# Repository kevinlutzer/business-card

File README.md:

# Electronic Business Card 

The purpose of this project was to demonstrate some of my skills as an Electrical Engineer to potential employers. This project required me to build and prototype a tri-state circuit, add controls with a STM32G ARM microcontroller and design/manufacture a custom printed circuit board. When you plug the device into a standard USB2A port it scrolls my portfolio website's URL across the matrix display. I designed this device to cost about $2.50 CAD per populated board. 

This idea was inspired by a piece of advice that Dave Jones, the owner of the [EEVblog](https://www.eevblog.com/) gave. He suggests that engineers should be bringing something to an interview to show that they can actually design and build things. I sent a later version of this project to Dave Jones with a programmer PCB which he opened on a [Mailbag Segment](https://youtu.be/45C6HFf2kIA?si=SCQMgJs3VvQc_wUq&t=3084). 

Currently I am using the project as a way to test and calibrate a pick and place machine.

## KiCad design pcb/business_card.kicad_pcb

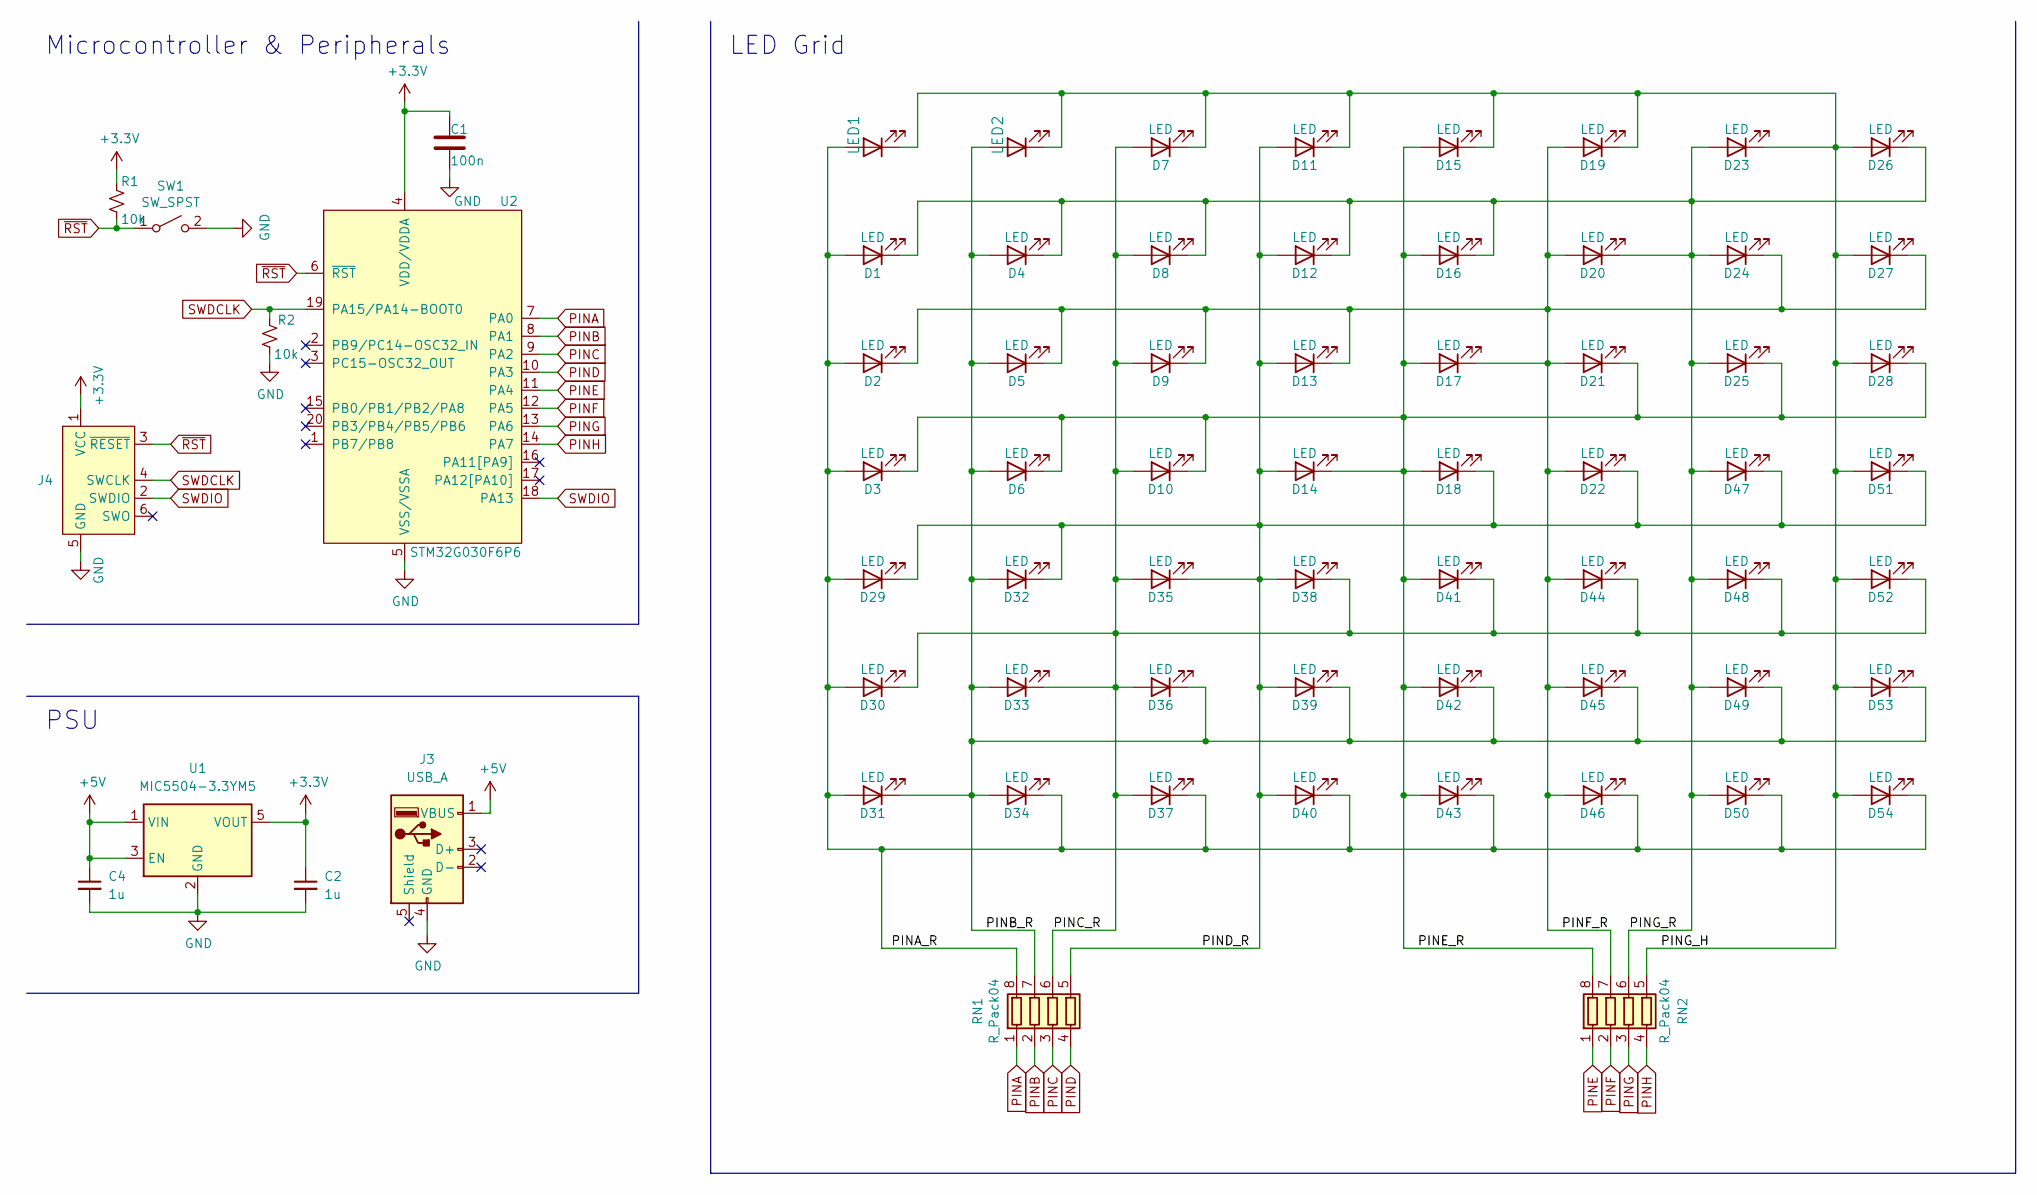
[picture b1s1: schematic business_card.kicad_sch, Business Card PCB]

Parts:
C1: 100n; C_0603_1608Metric
C2, C4: 1u; C_0603_1608Metric
D1, D2, D3, D4, D5, D6, D7, D8, D9, D10, D11, D12, D13, D14, D15, D16, D17, D18, D19, D20, D21, D22, D23, D24, D25, D26, D27, D28, D29, D30, D31, D32, D33, D34, D35, D36, D37, D38, D39, D40, D41, D42, D43, D44, D45, D46, D47, D48, D49, D50, D51, D52, D53, D54: LED; LED_0805_2012Metric
J3: USB_A; USB_A_PCB
J4: Conn_ARM_SWD_TagConnect_TC2030; Tag-Connect_TC2030-IDC-NL_2x03_P1.27mm_Vertical
LED1: LED; LED_0805_2012Metric
LED2: LED; D_0805_2012Metric
R1, R2: 10k; R_0603_1608Metric
RN1, RN2: R_Pack04; R_Array_Convex_4x1206
SW1: SW_SPST; SW_Push_1P1T_NO_CK_KMR2
U1: MIC5504-3.3YM5; SOT-23-5
U2: STM32G030F6P6; TSSOP-20_4.4x6.5mm_P0.65mm

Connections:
+3V3: C1.1, C2.1, J4.1 (VCC), R1.1, U1.5 (VOUT), U2.4 (VDD/VDDA)
+5V: C4.1, J3.1 (VBUS), U1.1 (VIN), U1.3 (EN)
/PINA_R: D1.2 (A), D2.2 (A), D3.2 (A), D29.2 (A), D30.2 (A), D31.2 (A), D34.1 (K), D37.1 (K), D40.1 (K), D43.1 (K), D46.1 (K), D50.1 (K), D54.1 (K), LED1.2 (A), RN1.8 (R1.2)
/PINB_R: D4.2 (A), D5.2 (A), D6.2 (A), D31.1 (K), D32.2 (A), D33.2 (A), D34.2 (A), D36.1 (K), D39.1 (K), D42.1 (K), D45.1 (K), D49.1 (K), D53.1 (K), LED2.2 (A), RN1.7 (R2.2)
/PINC_R: D7.2 (A), D8.2 (A), D9.2 (A), D10.2 (A), D30.1 (K), D33.1 (K), D35.2 (A), D36.2 (A), D37.2 (A), D38.1 (K), D41.1 (K), D44.1 (K), D48.1 (K), D52.1 (K), RN1.6 (R3.2)
/PIND_R: D11.2 (A), D12.2 (A), D13.2 (A), D14.2 (A), D18.1 (K), D22.1 (K), D29.1 (K), D32.1 (K), D35.1 (K), D38.2 (A), D39.2 (A), D40.2 (A), D47.1 (K), D51.1 (K), RN1.5 (R4.2)
/PINE_R: D3.1 (K), D6.1 (K), D10.1 (K), D14.1 (K), D15.2 (A), D16.2 (A), D17.2 (A), D18.2 (A), D21.1 (K), D25.1 (K), D28.1 (K), D41.2 (A), D42.2 (A), D43.2 (A), RN2.8 (R1.2)
/PINF_R: D2.1 (K), D5.1 (K), D9.1 (K), D13.1 (K), D17.1 (K), D19.2 (A), D20.2 (A), D21.2 (A), D22.2 (A), D24.1 (K), D27.1 (K), D44.2 (A), D45.2 (A), D46.2 (A), RN2.7 (R2.2)
/PING_H: D7.1 (K), D11.1 (K), D15.1 (K), D19.1 (K), D23.1 (K), D26.2 (A), D27.2 (A), D28.2 (A), D51.2 (A), D52.2 (A), D53.2 (A), D54.2 (A), LED1.1 (K), LED2.1 (K), RN2.5 (R4.2)
/PING_R: D1.1 (K), D4.1 (K), D8.1 (K), D12.1 (K), D16.1 (K), D20.1 (K), D23.2 (A), D24.2 (A), D25.2 (A), D26.1 (K), D47.2 (A), D48.2 (A), D49.2 (A), D50.2 (A), RN2.6 (R3.2)
GND: C1.2, C2.2, C4.2, J3.4 (GND), J4.5 (GND), R2.2, SW1.2 (B), U1.2 (GND), U2.5 (VSS/VSSA)
PINA: RN1.1 (R1.1), U2.7 (PA0)
PINB: RN1.2 (R2.1), U2.8 (PA1)
PINC: RN1.3 (R3.1), U2.9 (PA2)
PIND: RN1.4 (R4.1), U2.10 (PA3)
PINE: RN2.1 (R1.1), U2.11 (PA4)
PINF: RN2.2 (R2.1), U2.12 (PA5)
PING: RN2.3 (R3.1), U2.13 (PA6)
PINH: RN2.4 (R4.1), U2.14 (PA7)
SWDCLK: J4.4 (SWCLK), R2.1, U2.19 (PA15/PA14-BOOT0)
SWDIO: J4.2 (SWDIO), U2.18 (PA13)
~RST: J4.3 (~RESET), R1.2, SW1.1 (A), U2.6 (~RST)

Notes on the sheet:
Microcontroller & Peripherals
PSU
LED Grid

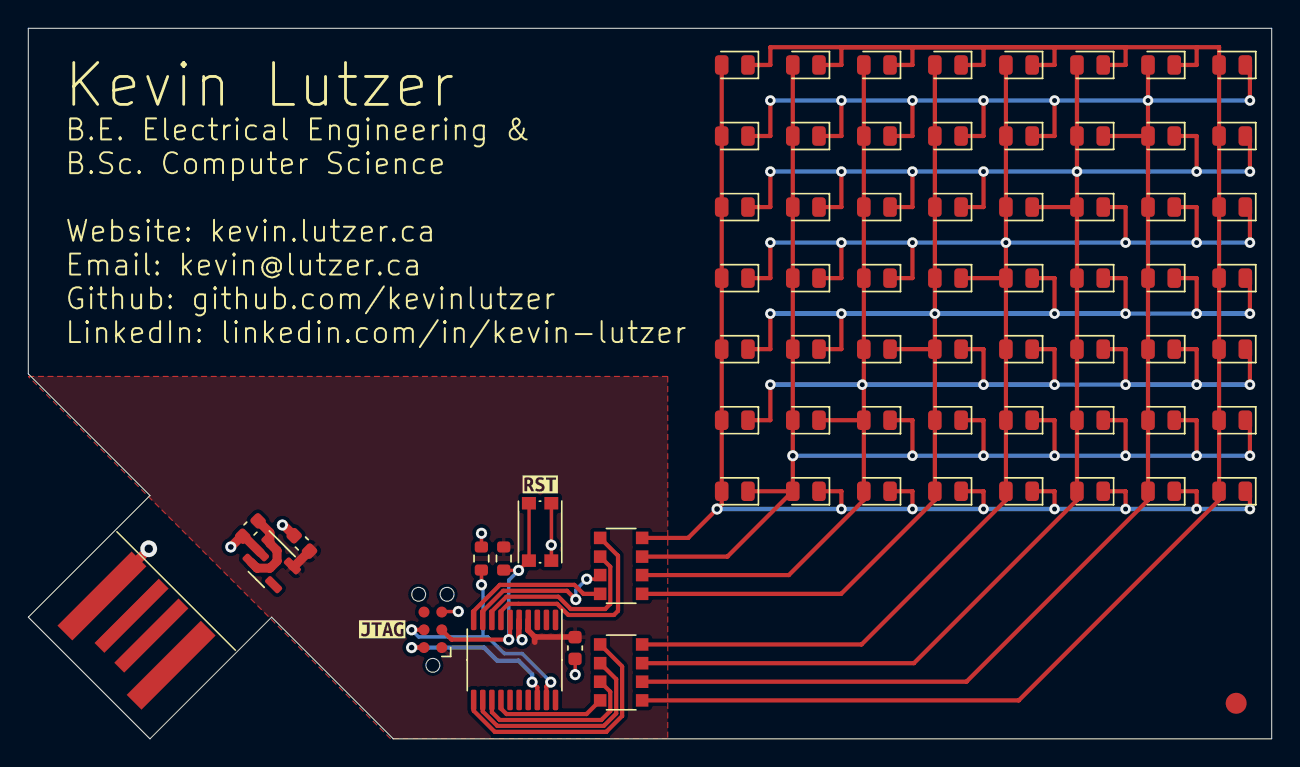
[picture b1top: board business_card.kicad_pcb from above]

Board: 2 copper layers, 88.9 x 50.8 mm, 70 parts (0 on the bottom side), 22 nets.

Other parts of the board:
kibuzzard-64BD977B: G***; kibuzzard-64BD977B
kibuzzard-64BD9765: G***; kibuzzard-64BD9765

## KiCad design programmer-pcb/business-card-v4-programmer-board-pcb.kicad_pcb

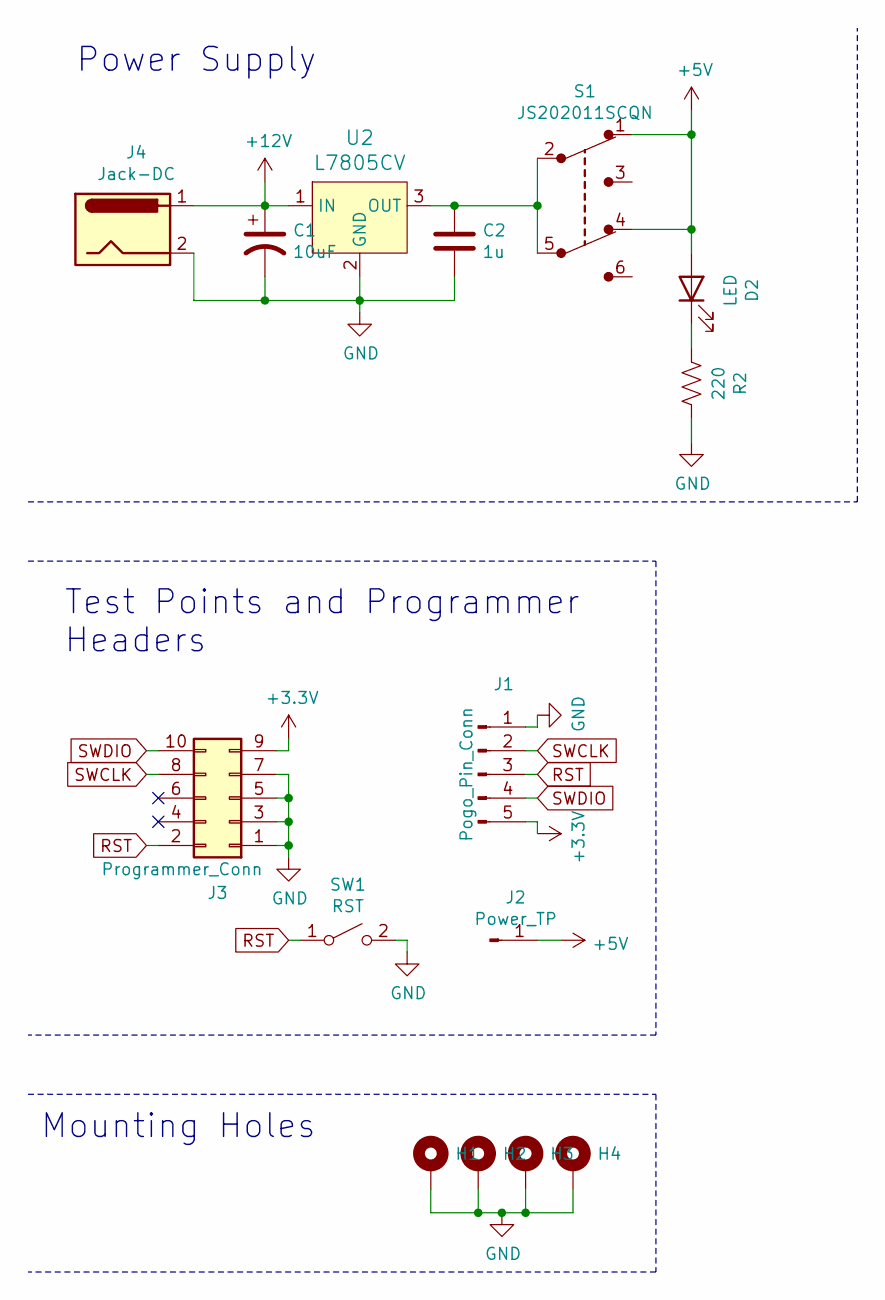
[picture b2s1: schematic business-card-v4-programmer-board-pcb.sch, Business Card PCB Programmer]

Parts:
C1: 10uF; C_Elec_5x5.4
C2: 1u; C_0603_1608Metric
D2: LED; LED_0805_2012Metric
H1, H2, H3, H4: MountingHole_Pad; MountingHole_3.5mm_Pad_Via
J1: Pogo_Pin_Conn; PinSocket_1x05_P2.54mm_Vertical
J2: Power_TP; PinSocket_1x01_P2.54mm_Vertical
J3: Programmer_Conn; PinSocket_2x05_P2.00mm_Vertical_SMD
J4: Jack-DC; BarrelJack_Horizontal
R2: 220; R_0805_2012Metric
S1: JS202011SCQN; Switch_Slide_JS202011SCQN; MPN JS202011SCQN; Digi-Key_PN 401-2002-1-ND
SW1: RST; SW_PUSH_6mm_H5mm
U2: L7805CV; TO-220-3; MPN L7805CV; Digi-Key_PN 497-1443-5-ND

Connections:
+3V3: J1.5, J3.9
+5V: D2.2 (A), J2.1, S1.1, S1.4
+12V: C1.1, J4.1, U2.1 (IN)
GND: C1.2, C2.2, H1.1, H2.1, H3.1, H4.1, J1.1, J3.1, J3.3, J3.5, J3.7, J4.2, R2.1, SW1.2 (B), U2.2 (GND)
unnamed: C2.1, S1.2, S1.5, U2.3 (OUT)
unnamed: D2.1 (K), R2.2
RST: J1.3, J3.2, SW1.1 (A)
SWCLK: J1.2, J3.8
SWDIO: J1.4, J3.10

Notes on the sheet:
Power Supply
Test Points and Programmer Headers
Mounting Holes

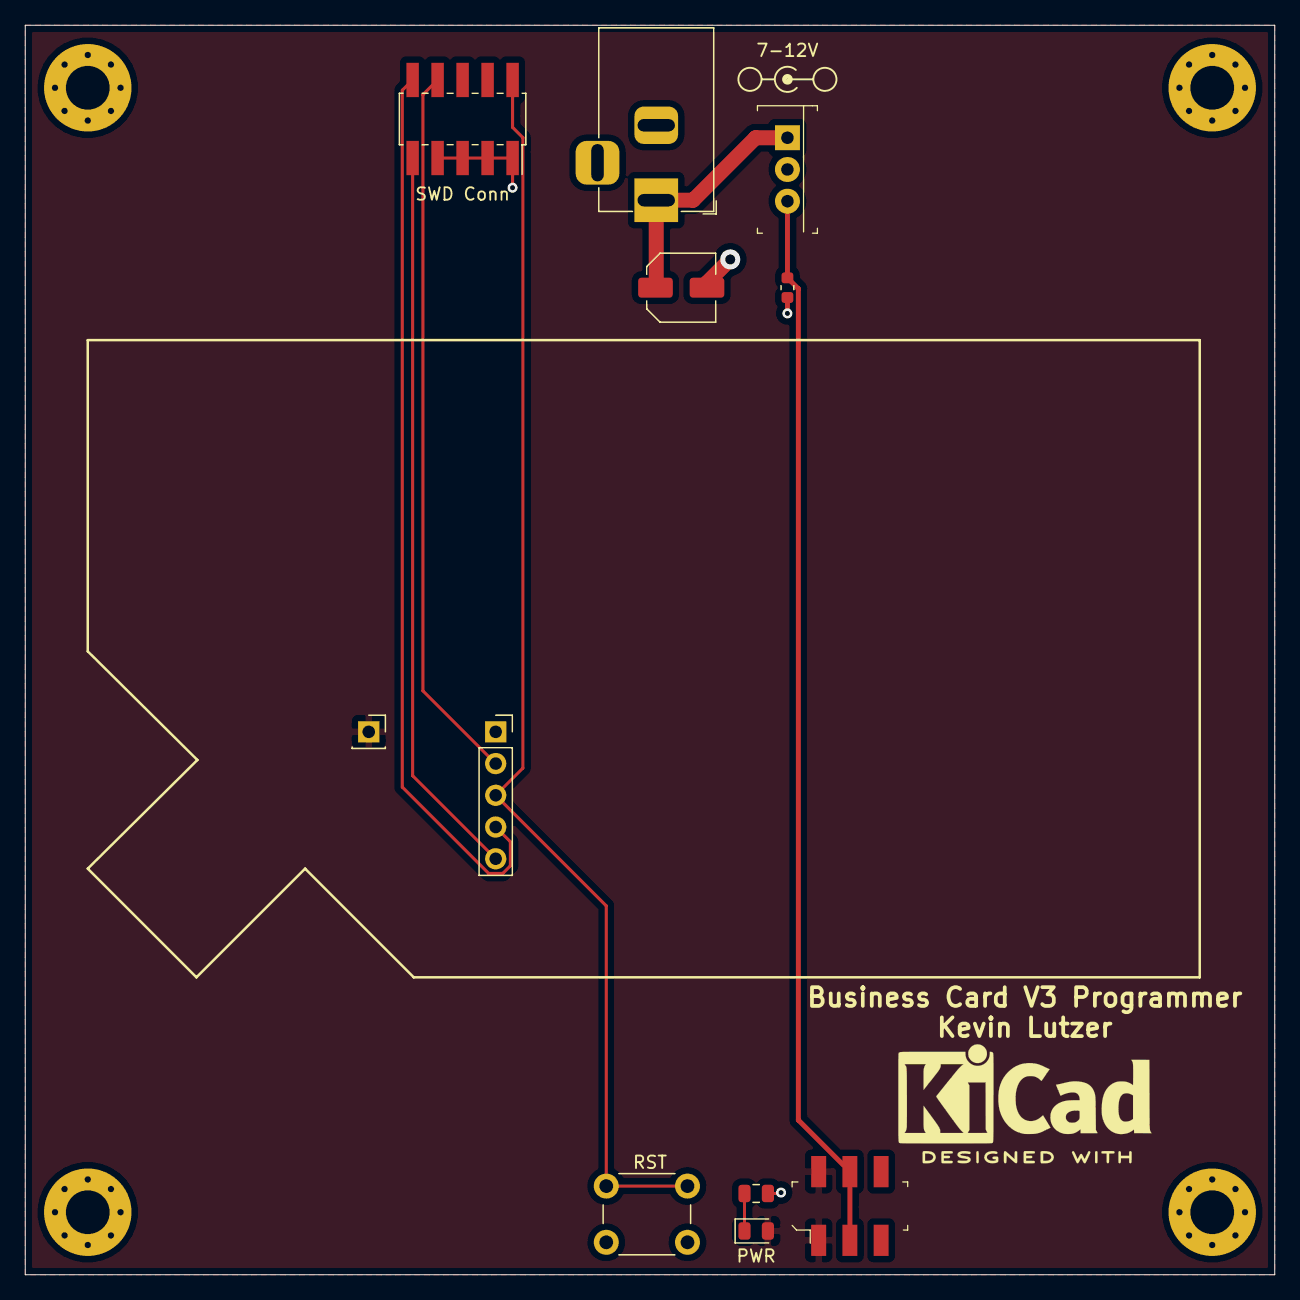
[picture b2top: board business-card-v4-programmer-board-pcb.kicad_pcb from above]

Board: 2 copper layers, 100.0 x 100.0 mm, 15 parts (0 on the bottom side), 9 nets.

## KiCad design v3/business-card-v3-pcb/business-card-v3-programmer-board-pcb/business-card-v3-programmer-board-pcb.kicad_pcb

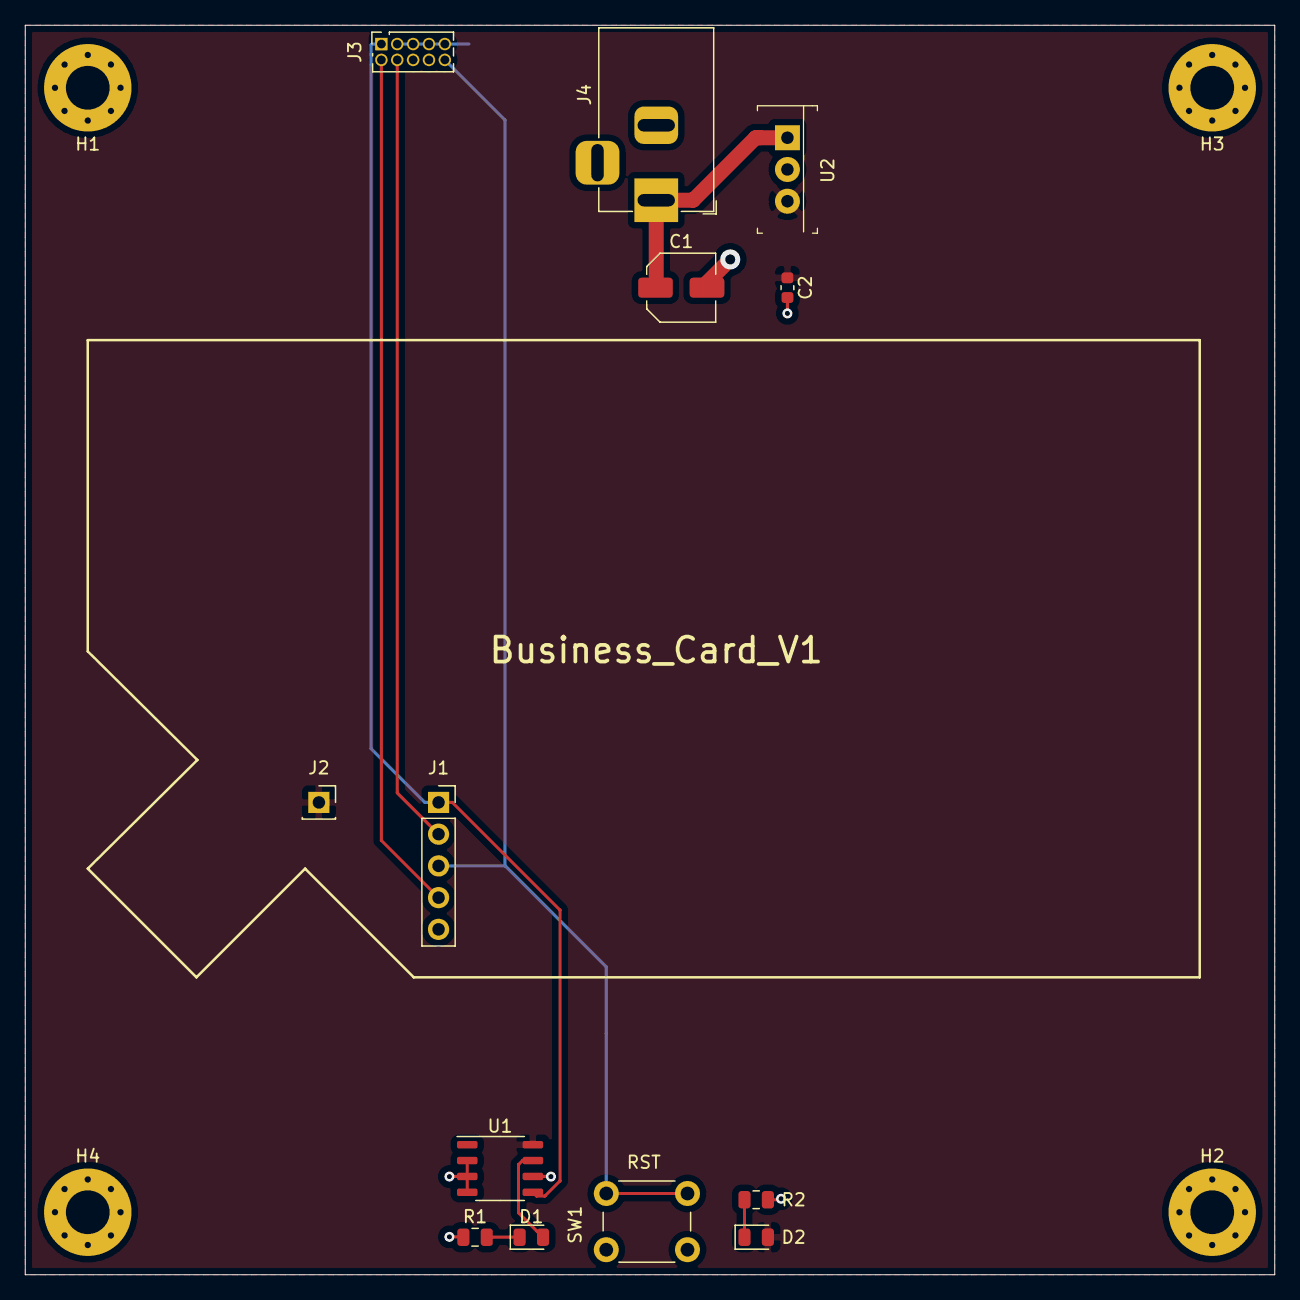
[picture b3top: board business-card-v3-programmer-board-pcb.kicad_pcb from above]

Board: 2 copper layers, 100.0 x 100.0 mm, 17 parts (0 on the bottom side), 10 nets.

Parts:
C1: 10uF; C_Elec_5x5.4
C2: 0.1u; C_0603_1608Metric
D1, D2: LED; LED_0805_2012Metric
H1, H2, H3, H4: MountingHole_Pad; MountingHole_3.5mm_Pad_Via
J1: Pogo_Pin_Conn; PinSocket_1x05_P2.54mm_Vertical
J2: Power_TP; PinSocket_1x01_P2.54mm_Vertical
J3: Programmer_Conn; PinSocket_2x05_P1.27mm_Vertical
J4: Jack-DC; BarrelJack_Horizontal
R1, R2: 220; R_0805_2012Metric
SW1: RST; SW_PUSH_6mm_H5mm
U1: LM2904; SOP-8_3.9x4.9mm_P1.27mm
U2: L7805CV; TO-220-3

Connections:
+3V3: J1.1, J3.1, U1.5
+5V: C2.1, D2.2, J2.1, U1.8, U2.3
+12V: C1.1, J4.1, U2.1
GND: C1.2, C2.2, H1.1, H2.1, H3.1, H4.1, J1.5, J3.3, J3.5, J3.7, J3.9, J4.2, R1.1, R2.1, SW1.2, U1.2, U1.3, U1.4, U1.6, U2.2
unnamed: D1.1, R1.2
unnamed: D1.2, U1.7
unnamed: D2.1, R2.2
RST: J1.3, J3.10, SW1.1
SWCLK: J1.2, J3.4
SWDIO: J1.4, J3.2

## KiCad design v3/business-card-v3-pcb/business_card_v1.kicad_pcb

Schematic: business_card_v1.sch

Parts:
C2, C3: 1u; C_0603_1608Metric
J1: Conn_01x05_Male; PinHeader_1x05_P2.54mm_Vertical
J2: Conn_01x01_Male; PinSocket_1x01_P2.54mm_Vertical
JP1: USBPCB; USB-A-PCB
LED1, LED2, LED3, LED4, LED5, LED6, LED7, LED8, LED9, LED10, LED11, LED12, LED13, LED14, LED15, LED16, LED17, LED18, LED19, LED20, LED21, LED22, LED23, LED24, LED25, LED26, LED27, LED28, LED29, LED30, LED31, LED32, LED33, LED34, LED35, LED36, LED37, LED38, LED39, LED40, LED41, LED42, LED43, LED44, LED45, LED46, LED47, LED48, LED49, LED50, LED51, LED52, LED53, LED54, LED55, LED56: LEDCHIPLED_0805; CHIPLED_0805
R1, R10: 10K; R_0603_1608Metric
RN1, RN2: R_Pack04; R_Array_Convex_4x0603
SW1: SW_SPST; SW_Push_1P1T_NO_CK_KMR2
U1: MIC5504-3.3YM5; SOT-23-5
U2: STM32G030F6P6; TSSOP-20_4.4x6.5mm_P0.65mm

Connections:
+3V3: C3.1, J1.5, R10.2, U1.5 (VOUT), U2.4
+5V: C2.1, J2.1, JP1.5V (VBUS), U1.1 (VIN), U1.3 (EN)
GND: C2.2, C3.2, J1.1, JP1.GND, R1.2, SW1.2, U1.2 (GND), U2.5
unnamed: LED1.A, LED9.A, LED17.A, LED25.A, LED33.A, LED41.A, LED49.A, LED50.C, LED51.C, LED52.C, LED53.C, LED54.C, LED55.C, LED56.C, RN1.8 (R1.2)
unnamed: LED1.C, LED2.C, LED3.C, LED4.C, LED5.C, LED6.C, LED7.C, LED8.A, LED16.A, LED24.A, LED32.A, LED40.A, LED48.A, LED56.A, RN2.5 (R4.2)
unnamed: LED2.A, LED10.A, LED18.A, LED26.A, LED34.A, LED42.A, LED43.C, LED44.C, LED45.C, LED46.C, LED47.C, LED48.C, LED49.C, LED50.A, RN1.7 (R2.2)
unnamed: LED7.A, LED8.C, LED9.C, LED10.C, LED11.C, LED12.C, LED13.C, LED14.C, LED15.A, LED23.A, LED31.A, LED39.A, LED47.A, LED55.A, RN2.6 (R3.2)
unnamed: LED3.A, LED11.A, LED19.A, LED27.A, LED35.A, LED36.C, LED37.C, LED38.C, LED39.C, LED40.C, LED41.C, LED42.C, LED43.A, LED51.A, RN1.6 (R3.2)
unnamed: LED4.A, LED12.A, LED20.A, LED28.A, LED29.C, LED30.C, LED31.C, LED32.C, LED33.C, LED34.C, LED35.C, LED36.A, LED44.A, LED52.A, RN1.5 (R4.2)
unnamed: LED5.A, LED13.A, LED21.A, LED22.C, LED23.C, LED24.C, LED25.C, LED26.C, LED27.C, LED28.C, LED29.A, LED37.A, LED45.A, LED53.A, RN2.8 (R1.2)
unnamed: LED6.A, LED14.A, LED15.C, LED16.C, LED17.C, LED18.C, LED19.C, LED20.C, LED21.C, LED22.A, LED30.A, LED38.A, LED46.A, LED54.A, RN2.7 (R2.2)
PINA: RN1.1 (R1.1), U2.7
PINB: RN1.2 (R2.1), U2.8
PINC: RN1.3 (R3.1), U2.9
PIND: RN1.4 (R4.1), U2.10
PINE: RN2.1 (R1.1), U2.11
PINF: RN2.2 (R2.1), U2.12
PING: RN2.3 (R3.1), U2.13
PINH: RN2.4 (R4.1), U2.14
RST: J1.3, R10.1, SW1.1, U2.6
SWDCLK-BOOT0: J1.2, R1.1, U2.19
SWDIO: J1.4, U2.18

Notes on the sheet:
Microcontroller & Peripherals
PSU
LED Grid

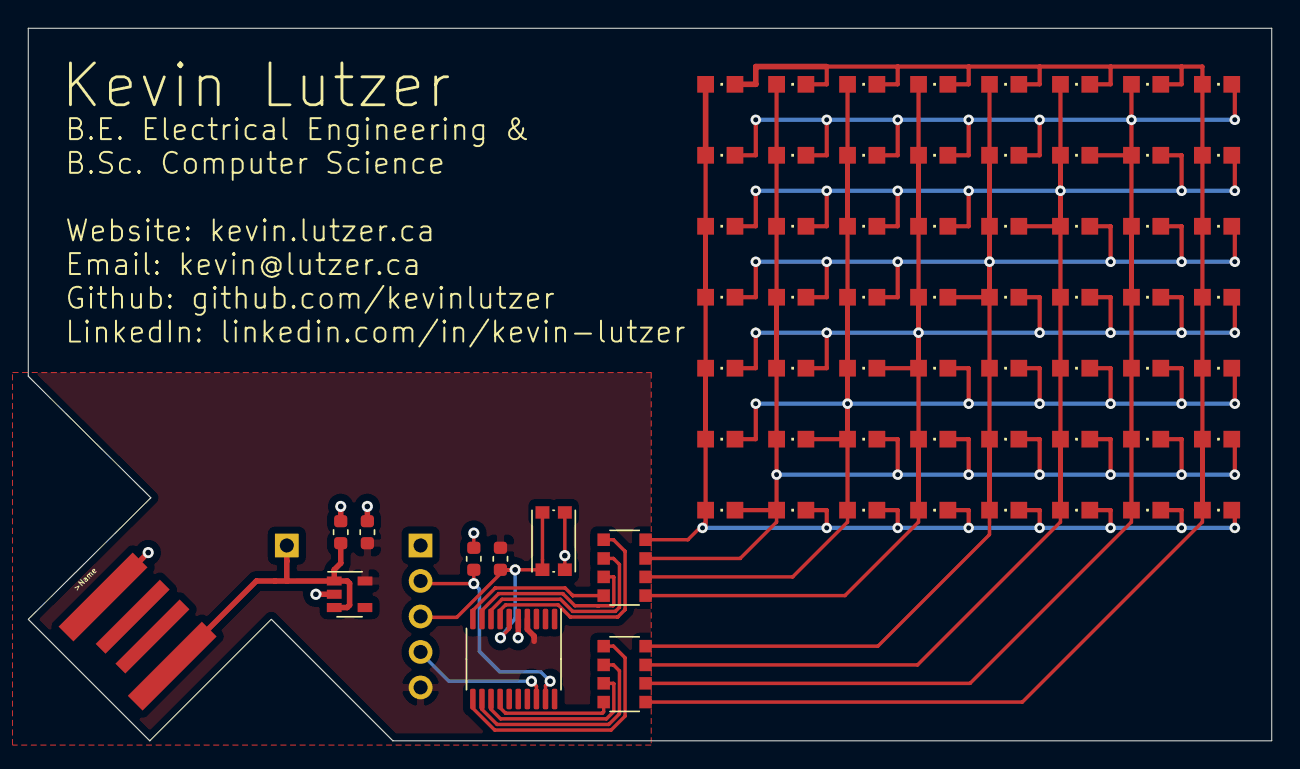
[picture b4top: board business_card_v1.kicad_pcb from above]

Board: 16 copper layers, 89.0 x 51.0 mm, 68 parts (0 on the bottom side), 22 nets.

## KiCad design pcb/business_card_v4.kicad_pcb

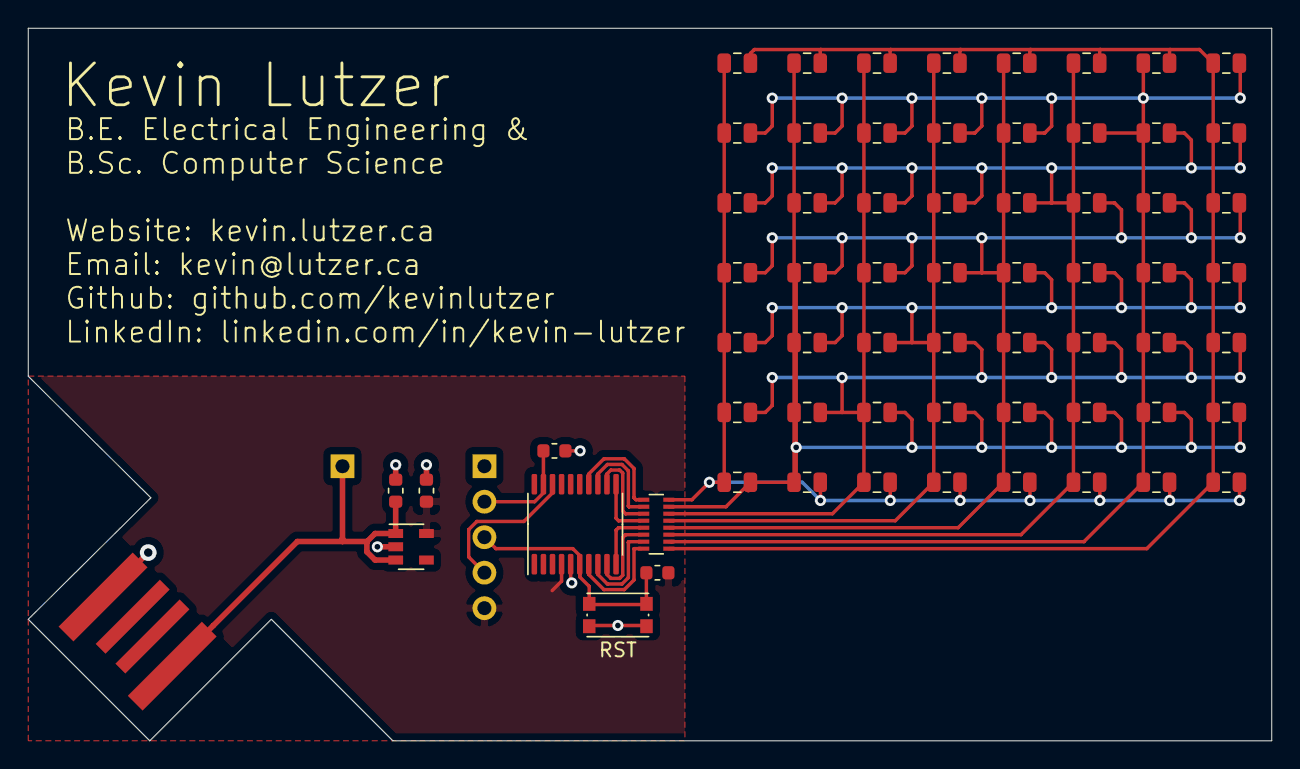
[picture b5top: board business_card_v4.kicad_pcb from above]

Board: 16 copper layers, 89.0 x 51.0 mm, 67 parts (0 on the bottom side), 22 nets.

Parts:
C2, C3: 1u; C_0603_1608Metric
D1, D2, D3, D4, D5, D6, D7, D8, D9, D10, D11, D12, D13, D14, D15, D16, D17, D18, D19, D20, D21, D22, D23, D24, D25, D26, D27, D28, D29, D30, D31, D32, D33, D34, D35, D36, D37, D38, D39, D40, D41, D42, D43, D44, D45, D46, D47, D48, D49, D50, D51, D52, D53, D54, D55, D56: LED; R_0805_2012Metric
J1: Conn_01x05_Male; PinHeader_1x05_P2.54mm_Vertical
J2: Conn_01x01_Male; PinHeader_1x01_P2.54mm_Vertical
J3: USB_A; USB-A-PCB
R1, R2: 10K; R_0603_1608Metric
RN1: R_Pack08; R_Array_Convex_8x0602
SW1: SW_SPST; SW_Push_1P1T_NO_CK_KMR2
U1: MIC5504-3.3YM5; SOT-23-5
U2: STM32G030F6P6; TSSOP-20_4.4x6.5mm_P0.65mm

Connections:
+3V3: C3.1, J1.5, R2.1, U1.5, U2.4
+5V: C2.1, J2.1, J3.1, U1.1, U1.3
GND: C2.2, C3.2, J1.1, J3.4, R1.2, SW1.2, U1.2, U2.5
unnamed: D1.1, D2.1, D3.1, D4.1, D5.1, D6.1, D7.1, D8.2, D16.2, D24.2, D32.2, D40.2, D48.2, D56.2, RN1.9
unnamed: D1.2, D9.2, D17.2, D25.2, D33.2, D41.2, D49.2, D50.1, D51.1, D52.1, D53.1, D54.1, D55.1, D56.1, RN1.16
unnamed: D7.2, D8.1, D9.1, D10.1, D11.1, D12.1, D13.1, D14.1, D15.2, D23.2, D31.2, D39.2, D47.2, D55.2, RN1.10
unnamed: D2.2, D10.2, D18.2, D26.2, D34.2, D42.2, D43.1, D44.1, D45.1, D46.1, D47.1, D48.1, D49.1, D50.2, RN1.15
unnamed: D3.2, D11.2, D19.2, D27.2, D35.2, D36.1, D37.1, D38.1, D39.1, D40.1, D41.1, D42.1, D43.2, D51.2, RN1.14
unnamed: D4.2, D12.2, D20.2, D28.2, D29.1, D30.1, D31.1, D32.1, D33.1, D34.1, D35.1, D36.2, D44.2, D52.2, RN1.13
unnamed: D5.2, D13.2, D21.2, D22.1, D23.1, D24.1, D25.1, D26.1, D27.1, D28.1, D29.2, D37.2, D45.2, D53.2, RN1.12
unnamed: D6.2, D14.2, D15.1, D16.1, D17.1, D18.1, D19.1, D20.1, D21.1, D22.2, D30.2, D38.2, D46.2, D54.2, RN1.11
PINA: RN1.8, U2.7
PINB: RN1.7, U2.8
PINC: RN1.6, U2.9
PIND: RN1.5, U2.10
PINE: RN1.4, U2.11
PINF: RN1.3, U2.12
PING: RN1.2, U2.13
PINH: RN1.1, U2.14
RST: J1.3, R2.2, SW1.1, U2.6
SWDCLK-BOOT0: J1.2, R1.1, U2.19
SWDIO: J1.4, U2.18

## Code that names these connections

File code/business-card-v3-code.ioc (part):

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PA6.GPIOParameters=PinState,GPIO_Label
Mcu.UserName=STM32G030F6Px
PA0.PinState=GPIO_PIN_RESET
PA0.GPIO_Label=PINA
PA3.GPIOParameters=GPIO_Label
PA6.PinState=GPIO_PIN_RESET
PA6.GPIO_Label=PING
PA2.GPIOParameters=GPIO_Label
PA7.PinState=GPIO_PIN_RESET
PA1.Signal=GPIO_Output
PA5.Signal=GPIO_Output
RCC.HSE_VALUE=8000000
PA4.GPIO_PuPd=GPIO_NOPULL
board=custom
PA1.GPIOParameters=GPIO_Label
PA1.GPIO_Label=PINB
PA4.GPIOParameters=GPIO_PuPd,GPIO_Label
Mcu.Name=STM32G030F6Px
PA2.Signal=GPIO_Output
PA0.Signal=GPIO_Output
PA4.Signal=GPIO_Output
RCC.SYSCLKFreq_VALUE=16000000
Mcu.Package=TSSOP20
PA6.Signal=GPIO_Output
PA7.GPIO_Label=PINH
PA5.GPIO_Label=PINF
PA2.GPIO_Label=PINC
PA0.GPIOParameters=PinState,GPIO_Label
PA5.GPIOParameters=GPIO_Label
PA4.GPIO_Label=PINE
PA7.GPIOParameters=PinState,GPIO_Label
PA3.GPIO_Label=PIND
PA3.Signal=GPIO_Output
PA7.Signal=GPIO_Output

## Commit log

2016-05-23 adding code and cad files to the repository
2016-07-15 deleted lock on .sch file
2016-07-15 changed folder names
2017-04-01 last commit before computer reset
2019-02-21 refactor and put everything in a v1
2020-01-19 add the base pcb files for the v2 design
2020-02-07 get the led layout right
2020-02-07 update pcb and schematic
2020-02-09 route the led grid, add the silk screen
2020-02-10 finish of the routing and get personal information on silk screen
2020-02-10 fix the business card design
2020-02-10 business card
2020-02-10 get the business card design done, looking for review now
2020-02-10 fix some of the silk screen
2020-02-10 add the gerber files
2020-02-11 more silk screen updates
2020-02-11 get the businss card completed
2020-02-11 update the 3d models
2020-02-12 update cards
2020-02-12 move the pcb_business_card
2020-02-13 remove DS_store
2020-02-13 add some text describing the business card project
2020-02-13 update to add the v1 and v2 board images
2020-02-13 add the what does it do section
2020-02-13 typo
2020-02-13 more typos
2020-02-18 get the published version completed
2020-03-03 refactor the readme, update project file
2020-03-04 try and setup the leds' gp
2020-03-04 more progress
2020-03-04 add the vstore code workspace file
2020-03-04 try and use the binary mehtod
2020-03-13 cleanup the code and remove the old constant
2020-03-13 update the code
2020-03-13 add the pcb boarder
2020-03-14 add the programming enclosure
2020-03-14 add the programmer case base file
2020-03-14 revert some changes to the v1 directory
2020-03-16 switch everything over to use cloud storage
2020-03-31 add the programming case
2020-03-31 name change of the business card PCB
2020-03-31 add the sck pad pin for miso and mosi
2020-03-31 add the zip file
2020-03-31 programmer pcb schematic
2020-03-31 finish the schematic
2020-03-31 start the pcb
2020-04-01 start populating some of the components
2020-04-02 finish the design
2020-04-02 add zip with gerber files
2020-05-04 add the v3 version of the pcb
2020-05-05 add the base import of the business card files
2020-05-07 finish pcb prototype for the card
2020-05-07 add code
2020-05-08 add the final touches to the Pcb
2020-05-09 add dimensions
2020-05-09 move everything before business-card-v3-pcb
2020-05-09 add the gerbers
2020-05-09 build out the majority of the board
2020-05-09 finish the pcb design
2020-05-10 move the programmer board files up a level
2020-05-10 regen all gerbers
2020-05-10 update to use a smaller resistor array
2020-05-14 add gerber files for the pcb
2020-05-14 move folders around to the top layer
2020-05-14 move the charlie_plexing files to the new business card code folder
2020-05-14 rename folders to be more generic
2020-05-14 move gerbers into the gerber folder for v3 design
2020-05-14 move gerbers around
2020-05-14 move gerber names around
2020-05-14 add gerbers for v2 and v3 programmers
2020-05-14 remove the v2 and v1 folder
2020-05-14 remove uneeded v3
2020-05-14 remove the gerber files
2020-05-14 cleanup
2020-05-24 bring back the correct revision of the v3 pcb
2020-05-24 remove the v3
2020-05-24 remove the gerber folder as I am using one at a different level
2020-05-24 remove the empty frame
2020-05-24 remove pcb footprints that are not needed
2020-05-24 remove the rescue library
2020-05-24 remove the rescue lib folder
2020-05-26 update the project config to have the correct outputs
2020-07-02 update code
2020-07-11 add the functions to display the leds correctly
2020-07-12 get a hi and smiley face working
2020-07-12 regen the Cubemx project
2020-07-12 update the source
2020-08-06 update card to v4
2020-08-06 create a net and update version of file names
2020-08-06 update pcb gerbers
2020-08-08 add the gerbers for the pcb programmer
2020-08-08 update the gerbers for the programemr pcb
2023-07-24 realign components on 0.01 inch grid, use solely kicad parts not eagle parts
2023-07-24 remove the progremmwer and the eagle files, rename everything to just business card
2023-07-24 make the v4 gerbers and ibom
2023-08-06 add updates
2023-10-07 rename documentation to assets
2023-10-07 remove business_card_v1 files
2023-10-07 use leds instead, add bom, update code
2023-10-07 add fab
2023-10-07 update changelog and readme
2023-10-07 use the LED footprint instead of diode footprint for LED2
2023-10-07 update and add some assets
